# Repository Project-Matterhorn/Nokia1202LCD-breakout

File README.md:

Nokia 1202 LCD breakout board
=============================

This is a simple Break-out board for the LCD found in Nokia 1202 phones.
The LCD is B/W 96x68px and driven by a 9bit SPI. 
The LCD terminates in a 12 pin 0.6mm pitch flex connector. 
It's tiny but still within the bounds of hand soldering.

The board is modelled on the Sparkfun 5110 breakout and shares 
the same pin-out in order to drop into an existing project.

## Additional Note by Zerrium
Changes:
1. Modified SMD and Capacitor footprint size from 0805 to 1206 hand solderable
2. Widen the copper traces

Schematic:

<br>
PCB:

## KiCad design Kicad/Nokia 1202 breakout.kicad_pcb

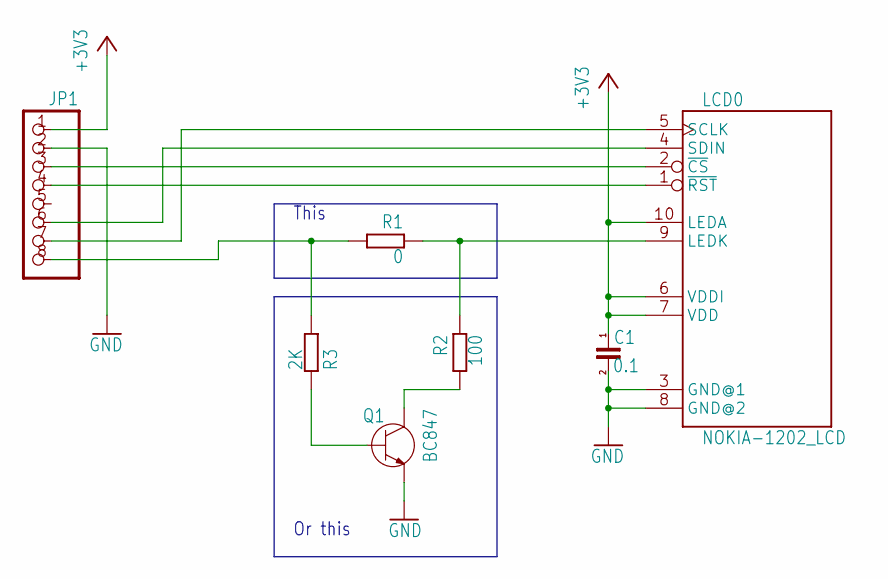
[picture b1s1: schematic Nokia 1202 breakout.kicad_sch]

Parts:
C1: 0.1; C_1206_3216Metric_Pad1.33x1.80mm_HandSolder
JP1: PINHD-1X8; 1X08
LCD0: NOKIA-1202_LCD
Q1: BC847; SOT23
R1: 0; R_1206_3216Metric_Pad1.30x1.75mm_HandSolder
R2: 100; R_1206_3216Metric_Pad1.30x1.75mm_HandSolder
R3: 2K; R_1206_3216Metric_Pad1.30x1.75mm_HandSolder

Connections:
+3V3: C1.1, JP1.1, LCD0.6 (VDDI), LCD0.7 (VDD), LCD0.10 (LEDA)
BL: JP1.8, R1.2, R3.2
GND: C1.2, JP1.2, LCD0.3 (GND@1), LCD0.8 (GND@2), Q1.2 (E)
MOSI: JP1.6, LCD0.4 (SDIN)
unnamed: JP1.3, LCD0.2 (~CS)
unnamed: JP1.4, LCD0.1 (~RST)
unnamed: LCD0.9 (LEDK), R1.1, R2.1
unnamed: Q1.1 (B), R3.1
unnamed: Q1.3 (C), R2.2
SCLK: JP1.7, LCD0.5 (SCLK)

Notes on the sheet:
This
Or this

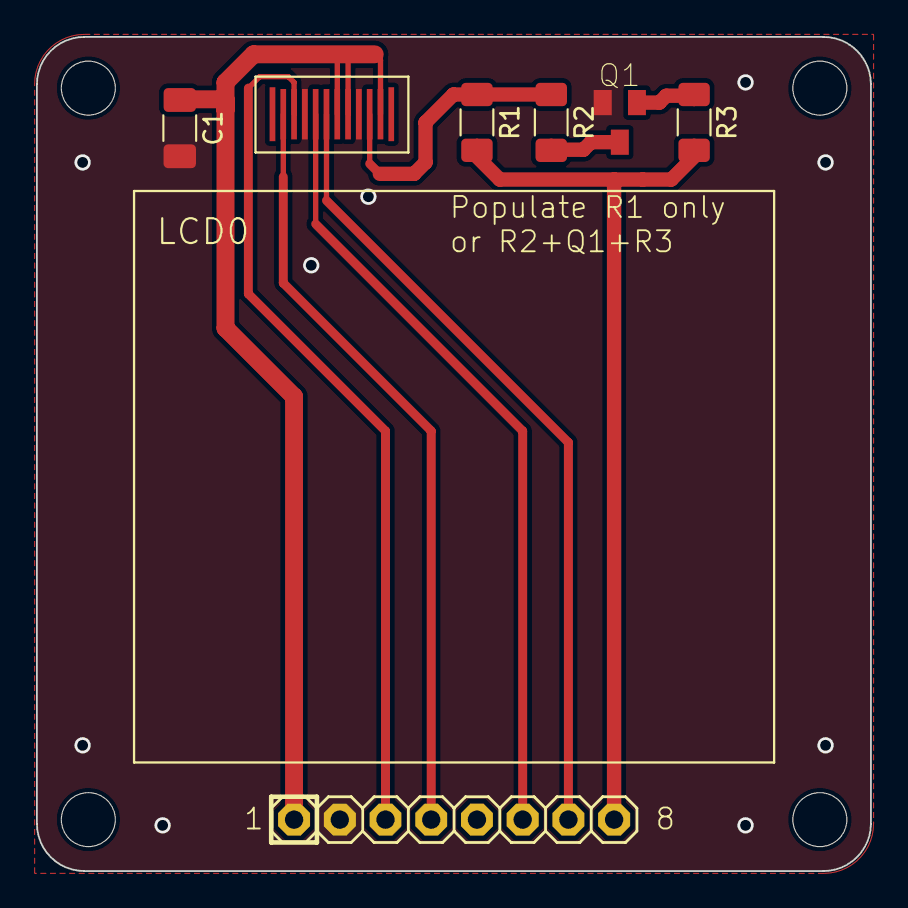
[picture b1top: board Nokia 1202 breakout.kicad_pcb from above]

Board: 2 copper layers, 46.3 x 46.3 mm, 11 parts (0 on the bottom side), 10 nets.

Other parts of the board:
UNK_HOLE_0: dummyfp0
UNK_HOLE_1: dummyfp1
UNK_HOLE_2: dummyfp2
UNK_HOLE_3: dummyfp3

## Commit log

2025-10-22 Added kicad files
